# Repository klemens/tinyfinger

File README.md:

# TinyFinger

TinyFinger is a small device powered by an ATtiny45 to produce pseudorandom
numbers for selecting student groups during the computer science hardware
courses at Leipzig University.

## board

The board is designed in KiCad and uses a single sided pcb layout using
mostly SMD components. The routing was done manually.

## code

The firmware for the ATtiny is written as an Arduino sketch using the
[ATTinyCore] board definitions. It uses a [linear congruential generator]
for generating pseudorandom numbers and transforms them to the needed
range using the gcc uniform_int_dist c++std implementation.

Flashing the firmware can be done using a normal Arduino programmes as an
ISP with the ArduinoISP example sketch included with the IDE. The PINs on
the board are from left to right: GND, MISO, VCC, SCK, MOSI, RESET.

## case

The case is modelled in Blender and intended for 3d printing, e.g. using
Cura after exporting the model as an stl file.

[ATTinyCore]: https://github.com/SpenceKonde/ATTinyCore
[linear congruential generator]: https://en.wikipedia.org/wiki/Linear_congruential_generator

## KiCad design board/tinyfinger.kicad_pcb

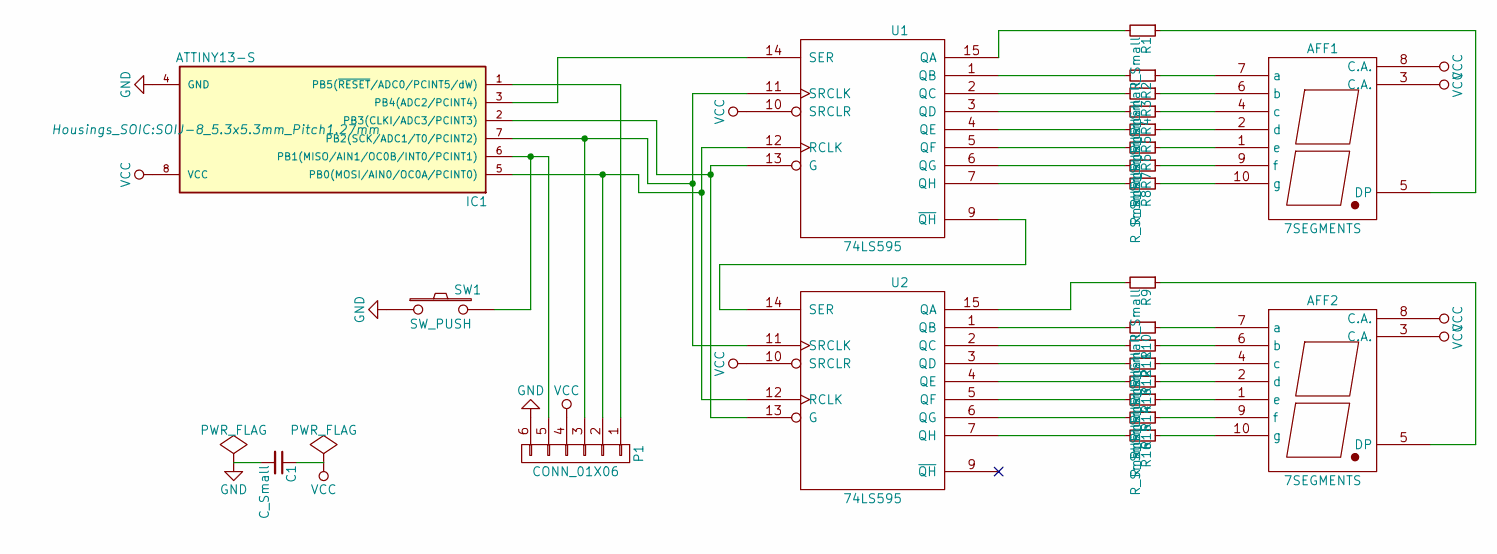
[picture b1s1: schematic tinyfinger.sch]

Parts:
AFF1, AFF2: 7SEGMENTS; 7SegmentLED_LTS6760_LTS6780
C1: C_Small; C_0805_HandSoldering
IC1: ATTINY13-S; SOIJ-8_5.3x5.3mm_Pitch1.27mm
P1: CONN_01X06; Pin_Header_Angled_1x06
R1, R2, R3, R4, R5, R6, R7, R8, R9, R10, R11, R12, R13, R14, R15, R16: R_Small; R_0805_HandSoldering
SW1: SW_PUSH; Switch_Shadow_Legostyle
U1, U2: 74LS595; DIP-16_W7.62mm_LongPads

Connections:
unnamed: AFF1.1 (e), R6.1
unnamed: AFF1.2 (d), R5.1
unnamed: AFF1.4 (c), R4.1
unnamed: AFF1.5 (DP), R1.1
unnamed: AFF1.6 (b), R3.1
unnamed: AFF1.7 (a), R2.1
unnamed: AFF1.9 (f), R7.1
unnamed: AFF1.10 (g), R8.1
unnamed: AFF2.1 (e), R14.1
unnamed: AFF2.2 (d), R13.1
unnamed: AFF2.4 (c), R12.1
unnamed: AFF2.5 (DP), R9.1
unnamed: AFF2.6 (b), R11.1
unnamed: AFF2.7 (a), R10.1
unnamed: AFF2.9 (f), R15.1
unnamed: AFF2.10 (g), R16.1
unnamed: IC1.1 (PB5(~RESET~/ADC0/PCINT5/dW)), P1.1
unnamed: IC1.2 (PB3(CLKI/ADC3/PCINT3)), U1.13 (G), U2.13 (G)
unnamed: IC1.3 (PB4(ADC2/PCINT4)), U1.14 (SER)
unnamed: IC1.5 (PB0(MOSI/AIN0/OC0A/PCINT0)), P1.2, U1.12 (RCLK), U2.12 (RCLK)
unnamed: IC1.7 (PB2(SCK/ADC1/T0/PCINT2)), P1.3, U1.11 (SRCLK), U2.11 (SRCLK)
unnamed: R1.2, U1.15 (QA)
unnamed: R2.2, U1.1 (QB)
unnamed: R3.2, U1.2 (QC)
unnamed: R4.2, U1.3 (QD)
unnamed: R5.2, U1.4 (QE)
unnamed: R6.2, U1.5 (QF)
unnamed: R7.2, U1.6 (QG)
unnamed: R8.2, U1.7 (QH)
unnamed: R9.2, U2.15 (QA)
unnamed: R10.2, U2.1 (QB)
unnamed: R11.2, U2.2 (QC)
unnamed: R12.2, U2.3 (QD)
unnamed: R13.2, U2.4 (QE)
unnamed: R14.2, U2.5 (QF)
unnamed: R15.2, U2.6 (QG)
unnamed: R16.2, U2.7 (QH)
unnamed: U1.9 (~QH), U2.14 (SER)
VCC: AFF1.3 (C.A.), AFF1.8 (C.A.), AFF2.3 (C.A.), AFF2.8 (C.A.), C1.1, IC1.8 (VCC), P1.4, U1.10 (SRCLR), U1.16 (VCC), U2.10 (SRCLR), U2.16 (VCC)

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
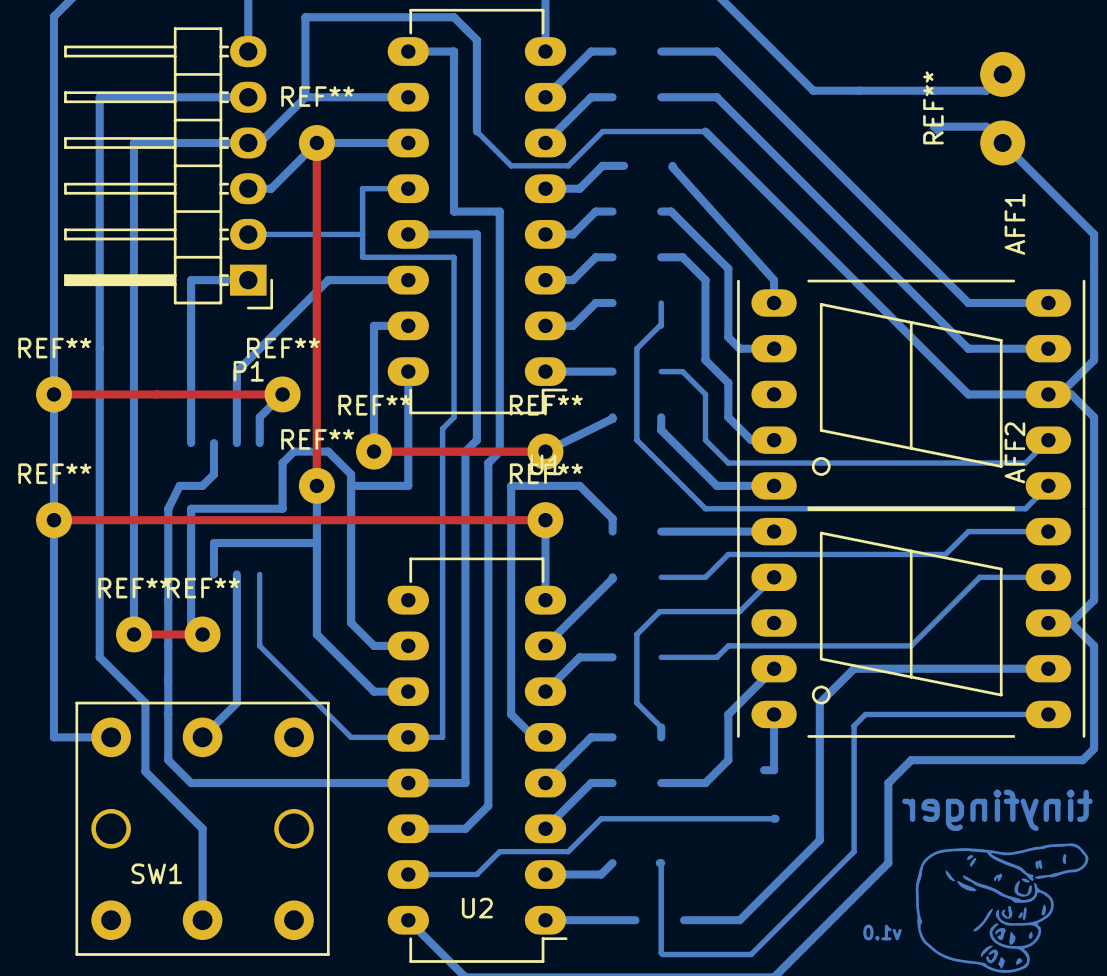
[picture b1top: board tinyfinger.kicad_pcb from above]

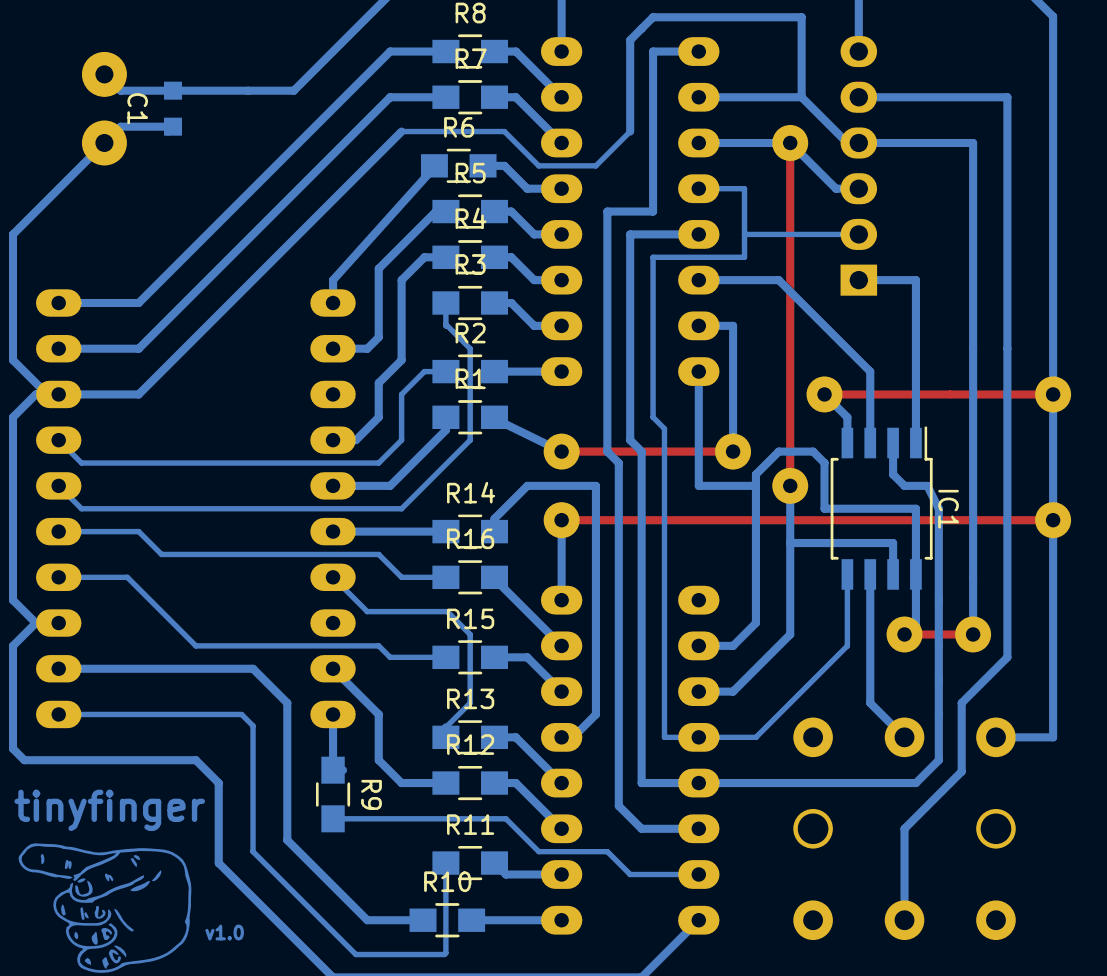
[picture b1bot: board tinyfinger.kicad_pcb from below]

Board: 2 copper layers, 25 parts (19 on the bottom side), 41 nets.

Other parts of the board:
svg2mod: G***; tinyfinger

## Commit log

2017-10-28 Import the kicad project for the board and related artwork
2017-10-28 Import the blender project for the case
2017-10-28 Import uniform_int_dist.h from gcc 7.1.0/7.2.0
2017-10-28 Import the arduino sketch for the random number generation
2017-10-28 Add README and licence under GPLv3
2017-11-06 Almost complete the case (rc1)
2017-11-09 Fix case battery height and add space for a mounting hole
2017-11-10 Add tinyfinger relief to the case
2017-11-17 Implement a slowing countdown on button request
2017-11-17 Don't show a leading zero for one-digit numbers
2017-11-17 Add state machines for recognizing different button presses
    For now single, double and long presses are supported.
2017-11-17 WIP: Use the state machines to control the finger
2017-11-19 WIP: Optimize/uglify the debounce state machine
2017-11-19 WIP: Use optimized distribute function and drop uniform_int_distribution
2017-11-19 Avoid unnecessary initialization of the display contents
2017-11-30 Use the state machines to control the finger
    Fixes uint16_t comparisons with millis(), removes DoublePressed state
    in button.h.
2017-12-01 Implements menu and ability to disable groups
2017-12-01 Update README
    Switch to an ATtiny45 and the ATTinyCore.
2018-02-19 Disable led display after 10 seconds to save energy
    Going to sleep and waking on an interrupt generated by the button would
    save even more energy, but it our current chip unfortunately has problems
    waking up reliably.
2018-02-19 WIP: Put ATtiny into standby when disabling the display
    Currently our chip does not wake from standby using either the external
    interrupt or the pin-change interrupt. It is unclear if this is a hard-
    or software problem.
2018-02-19 Document PIN-order in the README
